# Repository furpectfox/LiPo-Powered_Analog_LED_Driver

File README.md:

# Lipo-Powered Analog LED Driver
This circuit controls the dimming of an LED bar using only ICs and analog components&mdash;no microcontroller required. [Watch the demo here](https://youtu.be/S3qqzCgYGNY)

## [Click Me for Schematic](KiCad/schematic.pdf)

### Toggle ON/OFF
The circuit uses a push button to toggle power ON and OFF. In the OFF state, it consumes approximately 150 µA, due to current leakage through pull-up resistors.  

### Automatic Power Down
The circuit automatically shuts down when the voltage drops to 3V. However, even in the OFF state, it still consumes 150 µA, so it does not protect the battery from discharging comepletely.  

### Driving the LED with an N-Channel MOSFET
***Voltage Doubler***: The mosfet I'm using is a N-Channel MOSFET [IRF3205](https://www.infineon.com/dgdl/Infineon-IRF3205-DataSheet-v01_01-EN.pdf?fileId=5546d462533600a4015355def244190a). It has a Gate Threshold Voltage (Vgs) ranging from 2.0V to 4.0V. The normal operating voltage of a LiPo 18650 battery is 3.7V, and it decreases as the battery is being depleted. The solution is to have a voltage multiplier circuit to boost the voltage seen by the mosfet's gate to nearly twice the battery's voltage. This ensures the voltage driving the mosfet is always higher than the gate-source threshold voltage, even as the battery voltage decreases over time.  

The yellow trace shows the battery voltage (~4V). The blue trace shows the boosted voltage (~8V).  

***PWM Generator for Mosfet***:  
* A LM339 voltage comparator generates a ~800Hz square wave.
* This signal passes through a low-pass filter, converting it into a (somewhat) triangular waveform.
* A second voltage comparator compares this triangular waveform with a variable DC reference voltage (generated by a Resistor Selector Circuit).
* The result is a PWM signal with a controllable duty cycle, which drives the MOSFET gate and controls LED brightness.

Below is an example of a 25% duty cycle PWM signal:
* Top image: Triangular wave (blue) vs. DC reference voltage (yellow). Adjusting the level of the DC reference votlage will vary the duty cycle of the output square wave.
* Bottom image: Resulting gate drive signal (blue) (~8V amplitude).  

The circuit also allows a gradual voltage fall at the MOSFET gate, preventing high reverse voltage spikes at the drain (caused by long wiring acting as an inductor).

## Prototype

## PCB Layout
***The PCB layout was designed for homemade single-sided PCB fabrication using [this PCB plotter attachment](https://github.com/furpectfox/PCB_Trace_Plotter)***  

## Finish

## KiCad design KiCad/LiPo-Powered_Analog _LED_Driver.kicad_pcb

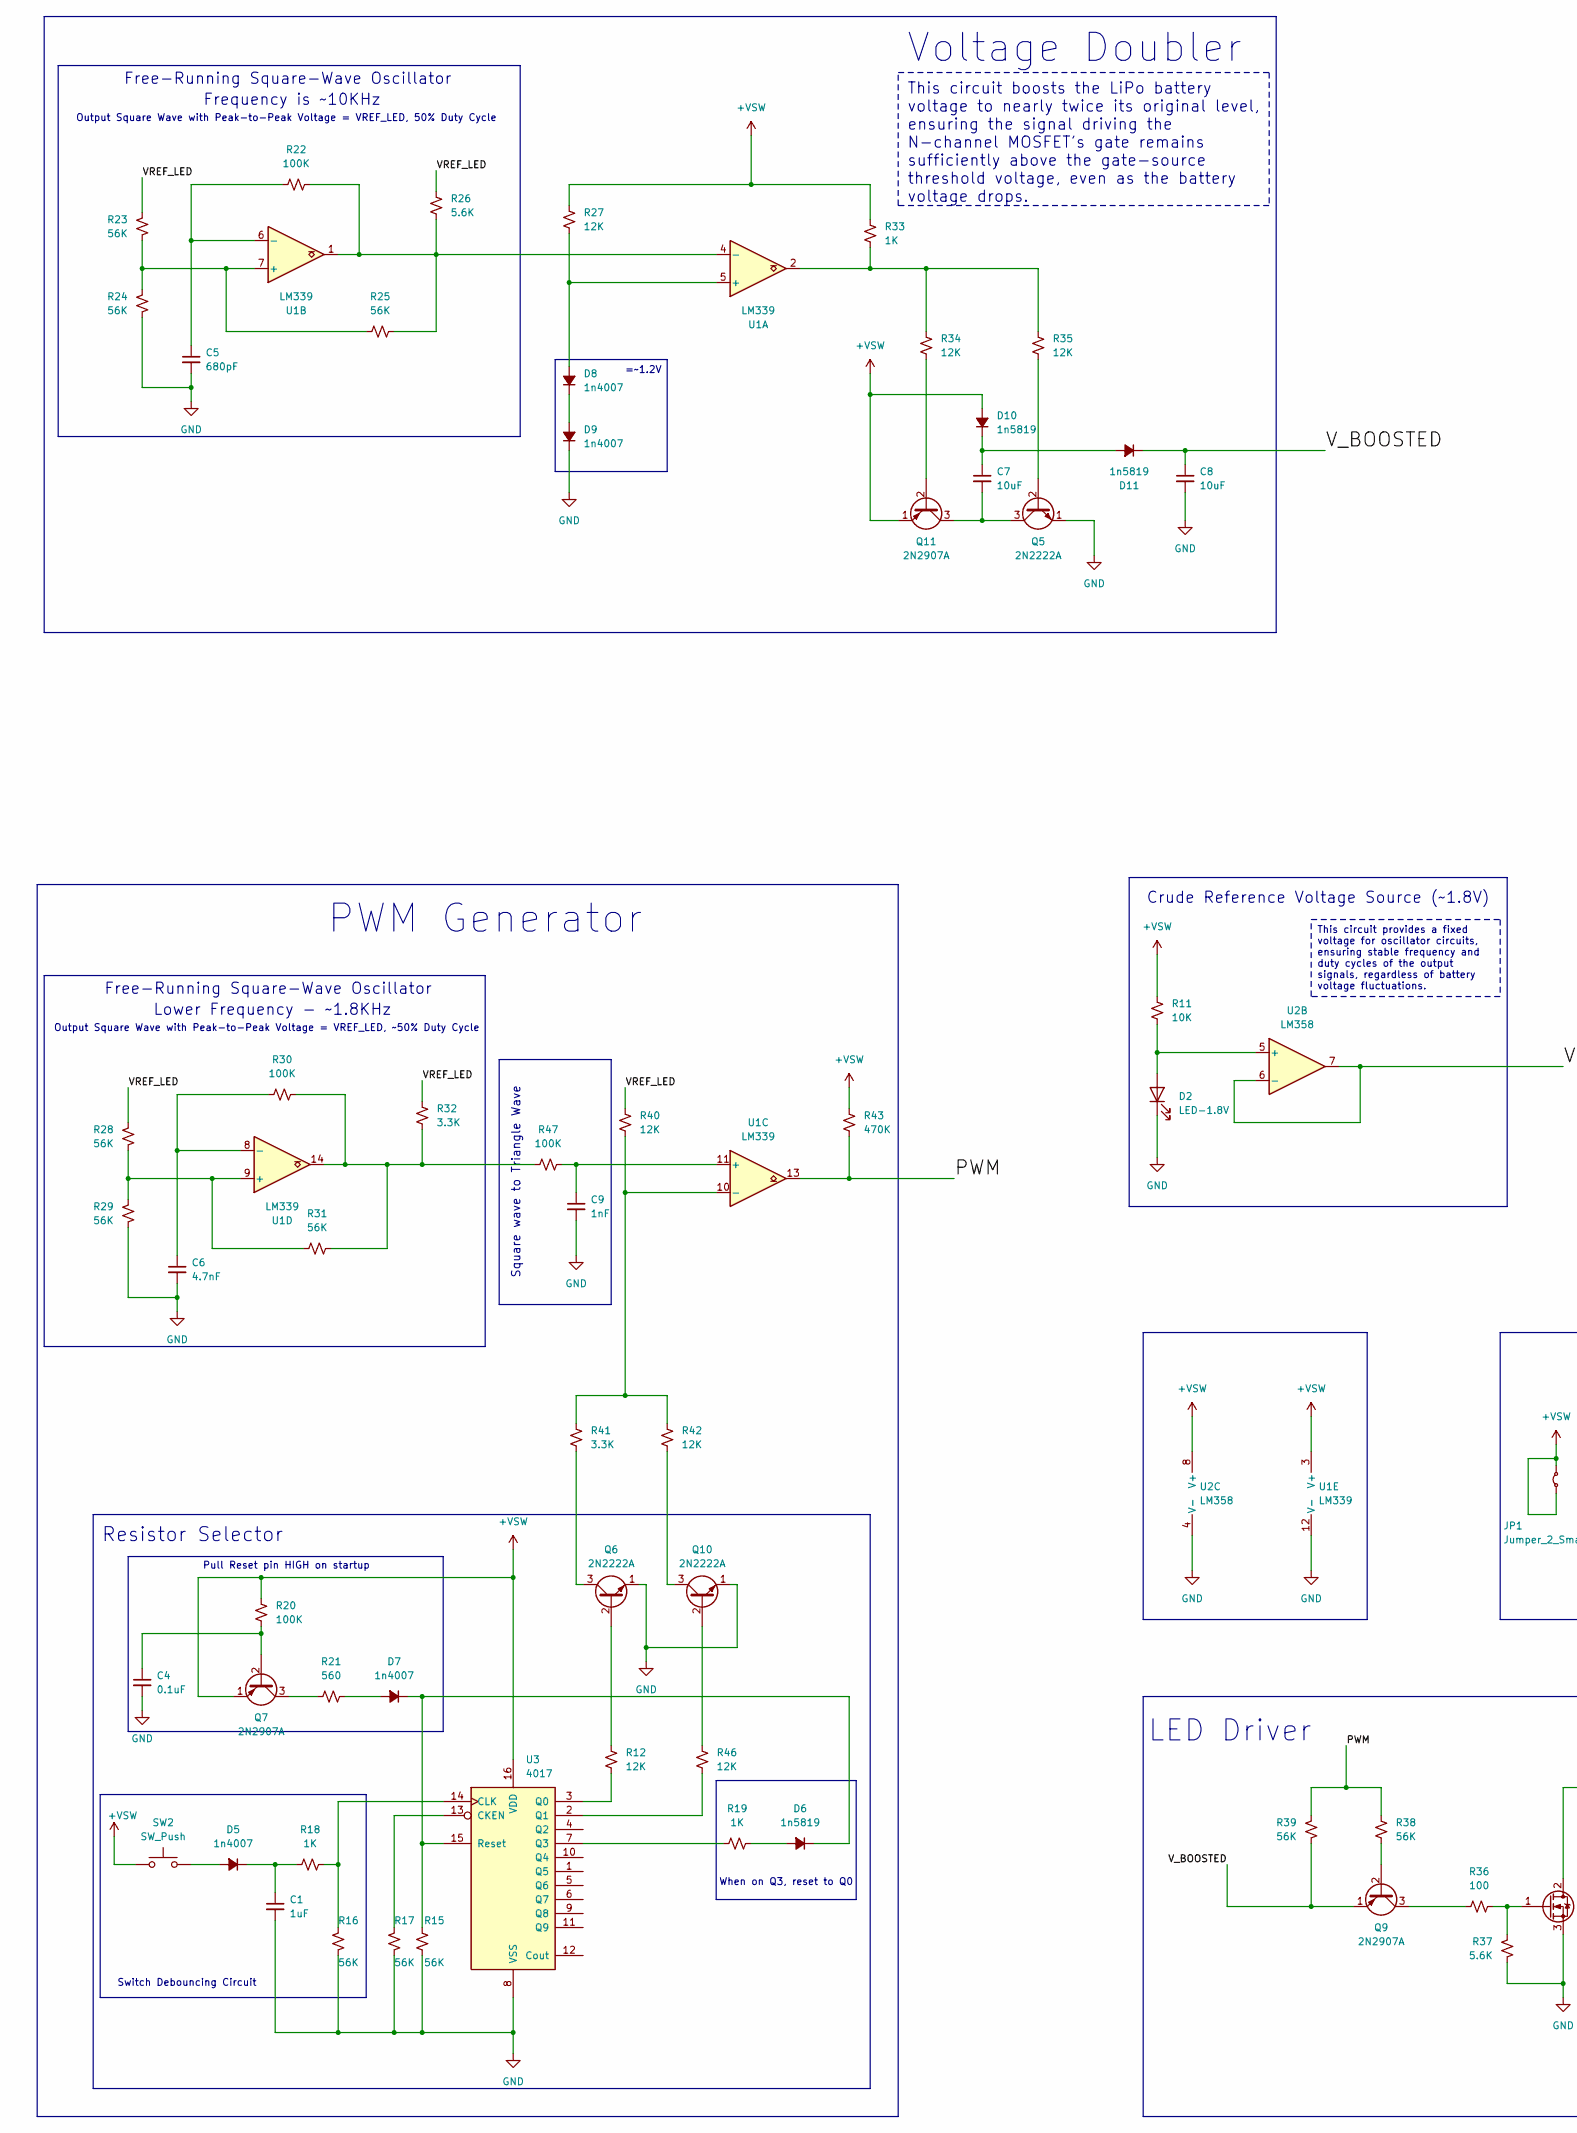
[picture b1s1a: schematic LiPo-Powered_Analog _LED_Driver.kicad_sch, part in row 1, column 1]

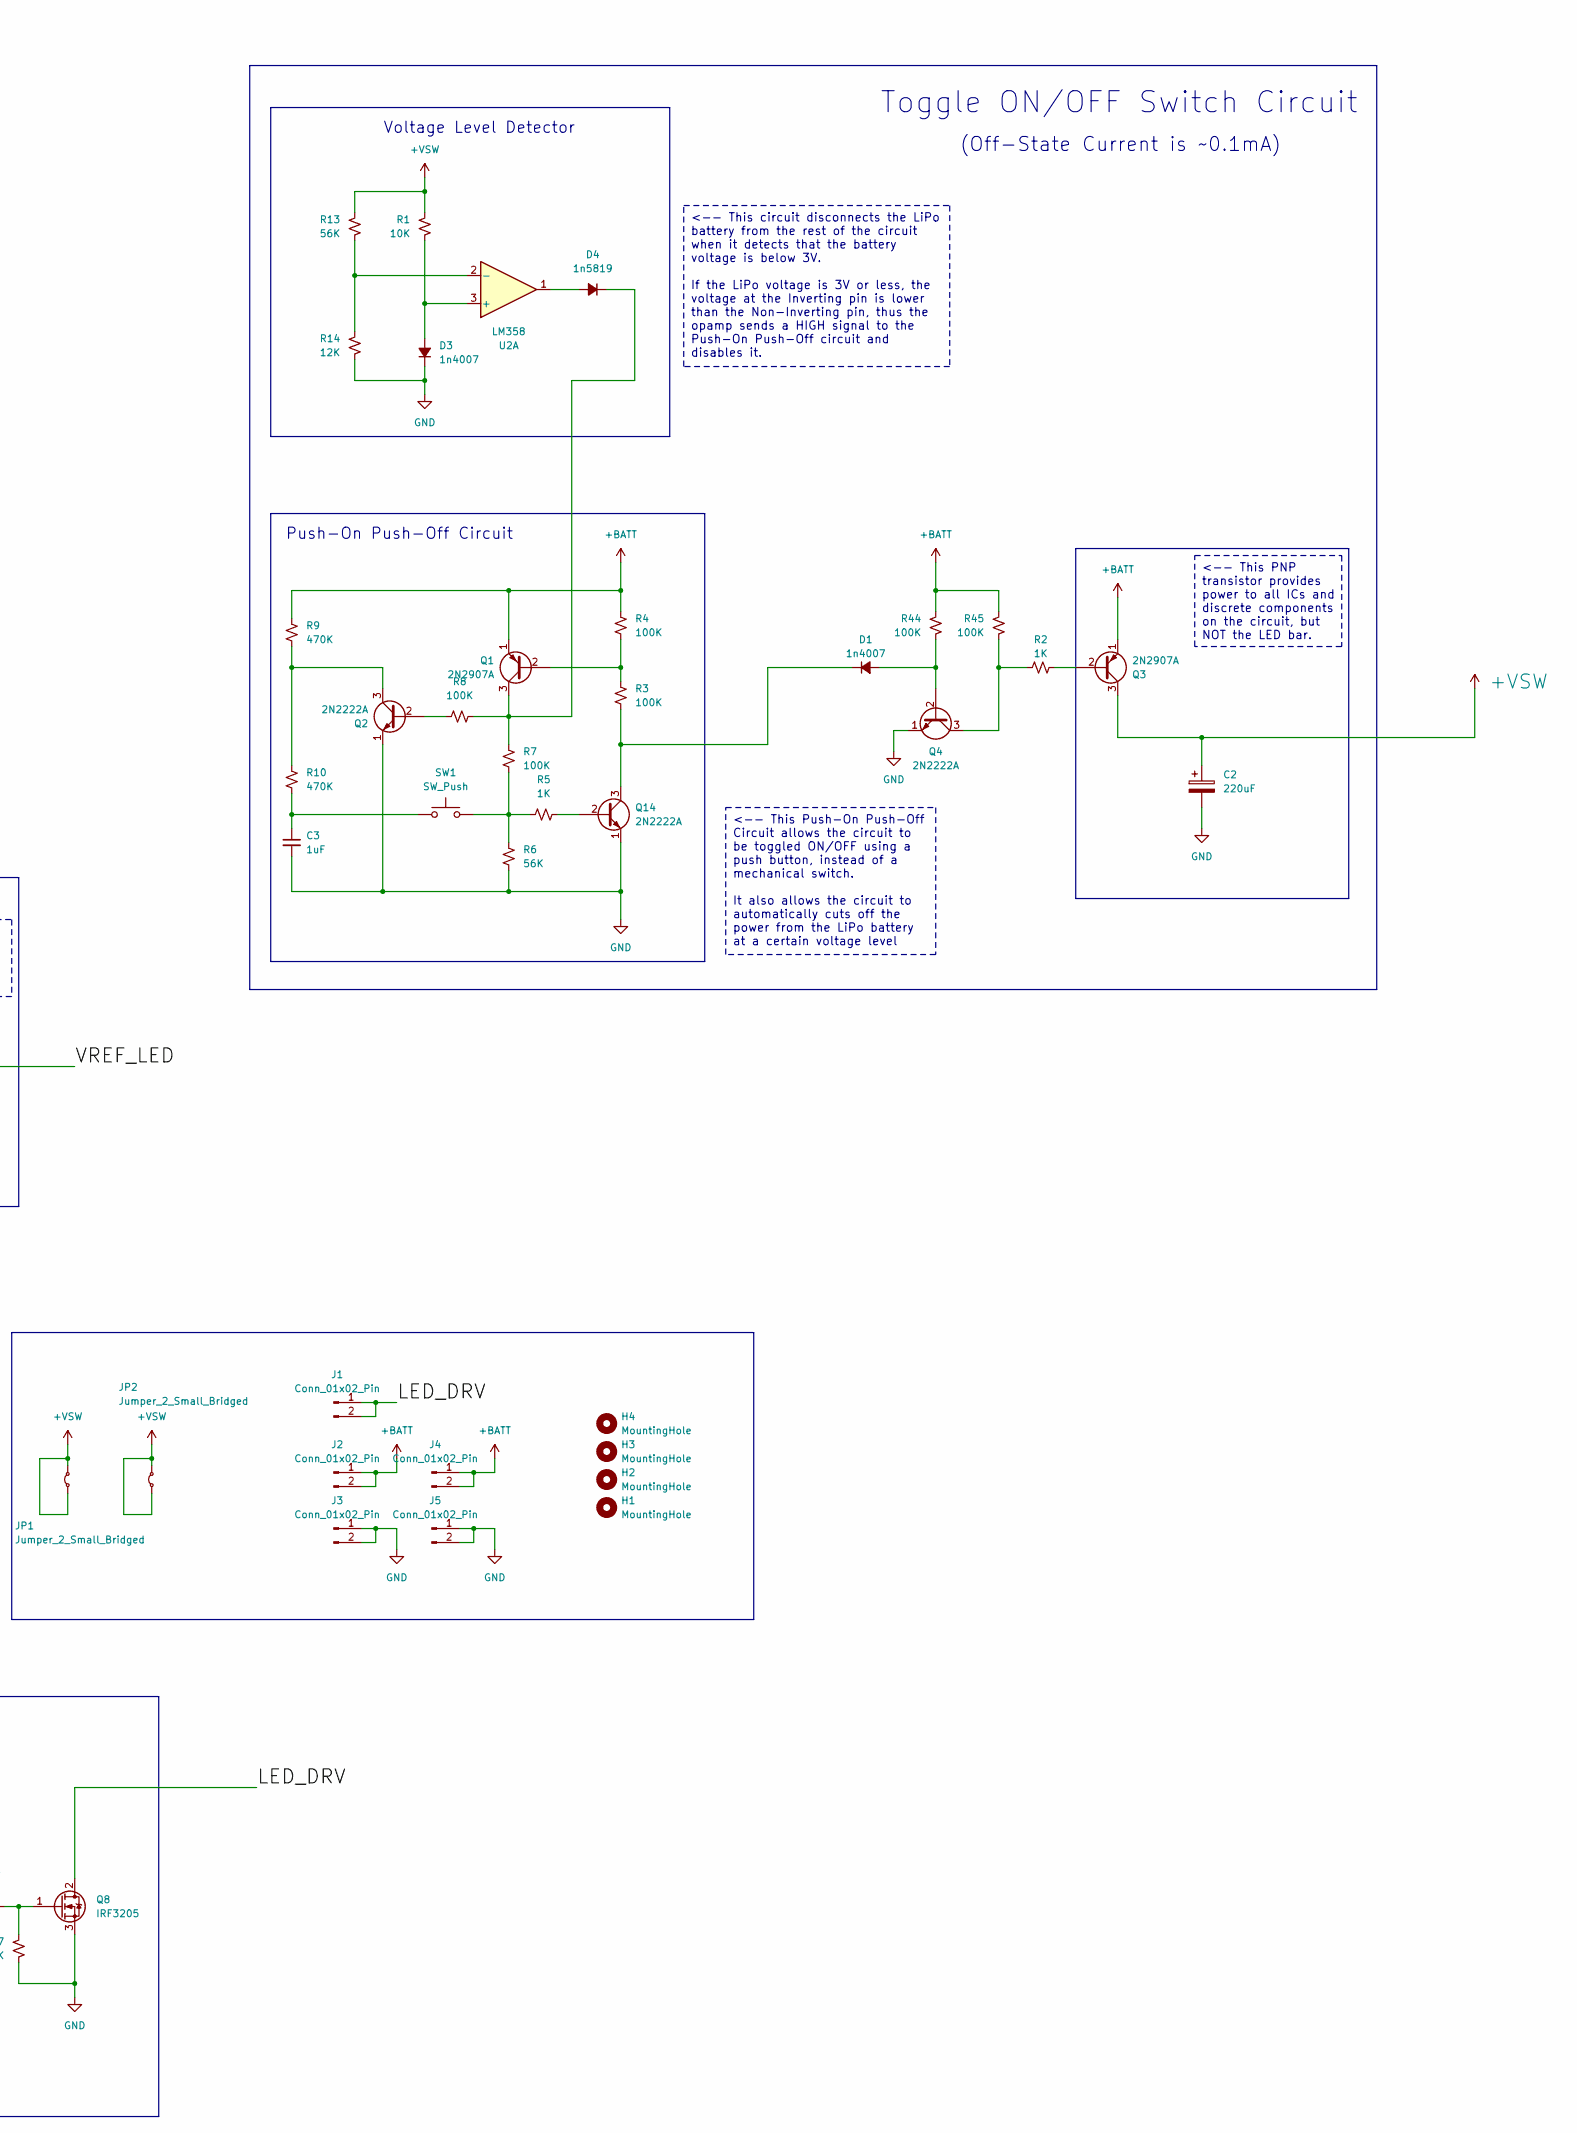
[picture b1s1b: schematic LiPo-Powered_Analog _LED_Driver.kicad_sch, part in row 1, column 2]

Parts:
C1, C3: 1uF; C_0603_1608Metric_Pad1.08x0.95mm_HandSolder
C2: 220uF; C_Radial_D6.3mm_H11.0mm_P2.50mm
C4: 0.1uF; C_0603_1608Metric_Pad1.08x0.95mm_HandSolder
C5: 680pF; C_0603_1608Metric_Pad1.08x0.95mm_HandSolder
C6: 4.7nF; C_0603_1608Metric_Pad1.08x0.95mm_HandSolder
C7, C8: 10uF; C_0603_1608Metric_Pad1.08x0.95mm_HandSolder
C9: 1nF; C_0603_1608Metric_Pad1.08x0.95mm_HandSolder
D1, D3, D5, D8, D9: 1n4007; D_SOD-123
D2: LED-1.8V; LED_0603_1608Metric_Pad1.05x0.95mm_HandSolder
D4, D6, D10, D11: 1n5819; D_A-405_P7.62mm_Horizontal
D7: 1n4007; D_A-405_P7.62mm_Horizontal
H1, H2, H3, H4: MountingHole; MountingHole_3.2mm_M3
J1, J2, J3, J4, J5: Conn_01x02_Pin; TestPoint_2Pads_Pitch5.08mm_Drill1.3mm
JP1, JP2: Jumper_2_Small_Bridged; TestPoint_2Pads_Pitch5.08mm_Drill1.3mm
Q1, Q3, Q7, Q9, Q11: 2N2907A; TO-92_Inline_Wide
Q2, Q4, Q5, Q6, Q10, Q14: 2N2222A; TO-92_Inline_Wide
Q8: IRF3205; TO-220-3_Horizontal_TabDown
R1: 10K; R_Axial_DIN0207_L6.3mm_D2.5mm_P7.62mm_Horizontal
R2, R5, R18, R19, R33: 1K; R_0603_1608Metric_Pad0.98x0.95mm_HandSolder
R3, R4, R7, R8, R20, R44, R45, R47: 100K; R_0603_1608Metric_Pad0.98x0.95mm_HandSolder
R6, R15, R16, R17, R23, R24, R29: 56K; R_0603_1608Metric_Pad0.98x0.95mm_HandSolder
R9, R10, R43: 470K; R_0603_1608Metric_Pad0.98x0.95mm_HandSolder
R11: 10K; R_0603_1608Metric_Pad0.98x0.95mm_HandSolder
R12, R40, R42, R46: 12K; R_Axial_DIN0207_L6.3mm_D2.5mm_P7.62mm_Horizontal
R13, R25, R28, R31, R38, R39: 56K; R_Axial_DIN0207_L6.3mm_D2.5mm_P7.62mm_Horizontal
R14, R27, R34, R35: 12K; R_0603_1608Metric_Pad0.98x0.95mm_HandSolder
R21: 560; R_0603_1608Metric_Pad0.98x0.95mm_HandSolder
R22, R30: 100K; R_Axial_DIN0207_L6.3mm_D2.5mm_P7.62mm_Horizontal
R26: 5.6K; R_Axial_DIN0207_L6.3mm_D2.5mm_P7.62mm_Horizontal
R32: 3.3K; R_0603_1608Metric_Pad0.98x0.95mm_HandSolder
R36: 100; R_0603_1608Metric_Pad0.98x0.95mm_HandSolder
R37: 5.6K; R_0603_1608Metric_Pad0.98x0.95mm_HandSolder
R41: 3.3K; R_Axial_DIN0207_L6.3mm_D2.5mm_P7.62mm_Horizontal
SW1, SW2: SW_Push; SolderWire-0.5sqmm_1x02_P4.6mm_D0.9mm_OD2.1mm
U1: LM339; DIP-14_W7.62mm
U2: LM358; DIP-8_W7.62mm
U3: 4017; DIP-16_W7.62mm

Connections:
+BATT: J2.1, J2.2, J4.1, J4.2, Q1.1 (E), Q3.1 (E), R4.1, R9.1, R44.1, R45.1
+VSW: C2.1, D10.2 (A), JP1.1 (A), JP1.2 (B), JP2.1 (A), JP2.2 (B), Q3.3 (C), Q7.1 (E), Q11.1 (E), R1.1, R11.1, R13.1, R20.1, R27.1, R33.1, R43.1, SW2.1, U1.3 (V+), U2.8 (V+), U3.16 (VDD)
/LED_DRV: J1.1, J1.2, Q8.2 (D)
/PWM: R38.2, R39.1, R43.2, U1.13
/VREF_LED: R23.1, R26.1, R28.1, R32.1, R40.1, U2.6 (-), U2.7
/V_BOOSTED: C8.1, D11.1 (K), Q9.1 (E), R39.2
GND: C1.2, C2.2, C3.2, C4.2, C5.2, C6.2, C8.2, C9.2, D2.1 (K), D3.1 (K), D9.1 (K), J3.1, J3.2, J5.1, J5.2, Q2.1 (E), Q4.1 (E), Q5.1 (E), Q6.1 (E), Q8.3 (S), Q10.1 (E), Q14.1 (E), R6.2, R14.2, R15.1, R16.1, R17.1, R24.2, R29.2, R37.1, U1.12 (V-), U2.4 (V-), U3.8 (VSS)
unnamed: C3.1, R10.2, SW1.1
unnamed: D1.2 (A), Q4.2 (B), R44.2
unnamed: D1.1 (K), Q14.3 (C), R3.2
unnamed: D2.2 (A), R11.2, U2.5 (+)
unnamed: D3.2 (A), R1.2, U2.3 (+)
unnamed: D4.2 (A), U2.1
unnamed: D4.1 (K), Q1.3 (C), R7.1, R8.2
unnamed: D5.2 (A), SW2.2
unnamed: C1.1, D5.1 (K), R18.1
unnamed: D6.2 (A), R19.2
unnamed: D6.1 (K), D7.1 (K), R15.2, U3.15 (Reset)
unnamed: D7.2 (A), R21.2
unnamed: D8.2 (A), R27.2, U1.5 (+)
unnamed: D8.1 (K), D9.2 (A)
unnamed: C7.1, D10.1 (K), D11.2 (A)
unnamed: Q1.2 (B), R3.1, R4.2
unnamed: Q2.2 (B), R8.1
unnamed: Q2.3 (C), R9.2, R10.1
unnamed: Q3.2 (B), R2.2
unnamed: Q4.3 (C), R2.1, R45.2
unnamed: Q5.2 (B), R35.1
unnamed: Q6.2 (B), R12.1
unnamed: Q6.3 (C), R41.2
unnamed: C4.1, Q7.2 (B), R20.2
unnamed: Q7.3 (C), R21.1
unnamed: Q8.1 (G), R36.2, R37.2
unnamed: Q9.2 (B), R38.1
unnamed: Q9.3 (C), R36.1
unnamed: Q10.2 (B), R46.1
unnamed: Q10.3 (C), R42.2
unnamed: Q11.2 (B), R34.1
unnamed: C7.2, Q5.3 (C), Q11.3 (C)
unnamed: Q14.2 (B), R5.2
unnamed: R5.1, R6.1, R7.2, SW1.2
unnamed: R30.2, R31.2, R32.2, R47.1, U1.14
unnamed: R33.2, R34.2, R35.2, U1.2
unnamed: R22.2, R25.2, R26.2, U1.1, U1.4 (-)
unnamed: R23.2, R24.1, R25.1, U1.7 (+)
unnamed: C5.1, R22.1, U1.6 (-)
unnamed: C9.1, R47.2, U1.11 (+)
unnamed: R40.2, R41.1, R42.1, U1.10 (-)
unnamed: R28.2, R29.1, R31.1, U1.9 (+)
unnamed: C6.1, R30.1, U1.8 (-)
unnamed: R13.2, R14.1, U2.2 (-)
unnamed: R17.2, U3.13 (CKEN)
unnamed: R16.2, R18.2, U3.14 (CLK)
unnamed: R12.2, U3.3 (Q0)
unnamed: R46.2, U3.2 (Q1)
unnamed: R19.1, U3.7 (Q3)

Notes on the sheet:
<-- This circuit disconnects the LiPo battery from the rest of the circuit when it detects that the battery voltage is below 3V. If the LiPo voltage is 3V or less, the voltage at the Inverting pin is lower than the Non-Inverting pin, thus the opamp sends a HIGH signal to the Push-On Push-Off circui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
This circuit boosts the LiPo battery voltage to nearly twice its original level, ensuring the signal driving the N-channel MOSFET's gate remains sufficiently above the gate-source threshold voltage, even as the battery voltage drops.
<-- This Push-On Push-Off Circuit allows the circuit to be toggled ON/OFF using a push button, instead of a mechanical switch. It also allows the circuit to automatically cuts off the power from the LiPo battery at a certain voltage level
<-- This PNP transistor provides power to all ICs and discrete components on the circuit, but NOT the LED bar.
This circuit provides a fixed voltage for oscillator circuits, ensuring stable frequency and duty cycles of the output signals, regardless of battery voltage fluctuations.
LED Driver
Frequency is ~10KHz
Crude Reference Voltage Source (~1.8V)
Voltage Level Detector
Free-Running Square-Wave Oscillator
Push-On Push-Off Circuit
PWM Generator
Output Square Wave with Peak-to-Peak Voltage = VREF_LED, 50% Duty Cycle
Resistor Selector
Lower Frequency - ~1.8KHz
Toggle ON/OFF Switch Circuit
Square wave to Triangle Wave
When on Q3, reset to Q0
Output Square Wave with Peak-to-Peak Voltage = VREF_LED, ~50% Duty Cycle
(Off-State Current is ~0.1mA)
Voltage Doubler
=~1.2V
Pull Reset pin HIGH on startup
Switch Debouncing Circuit

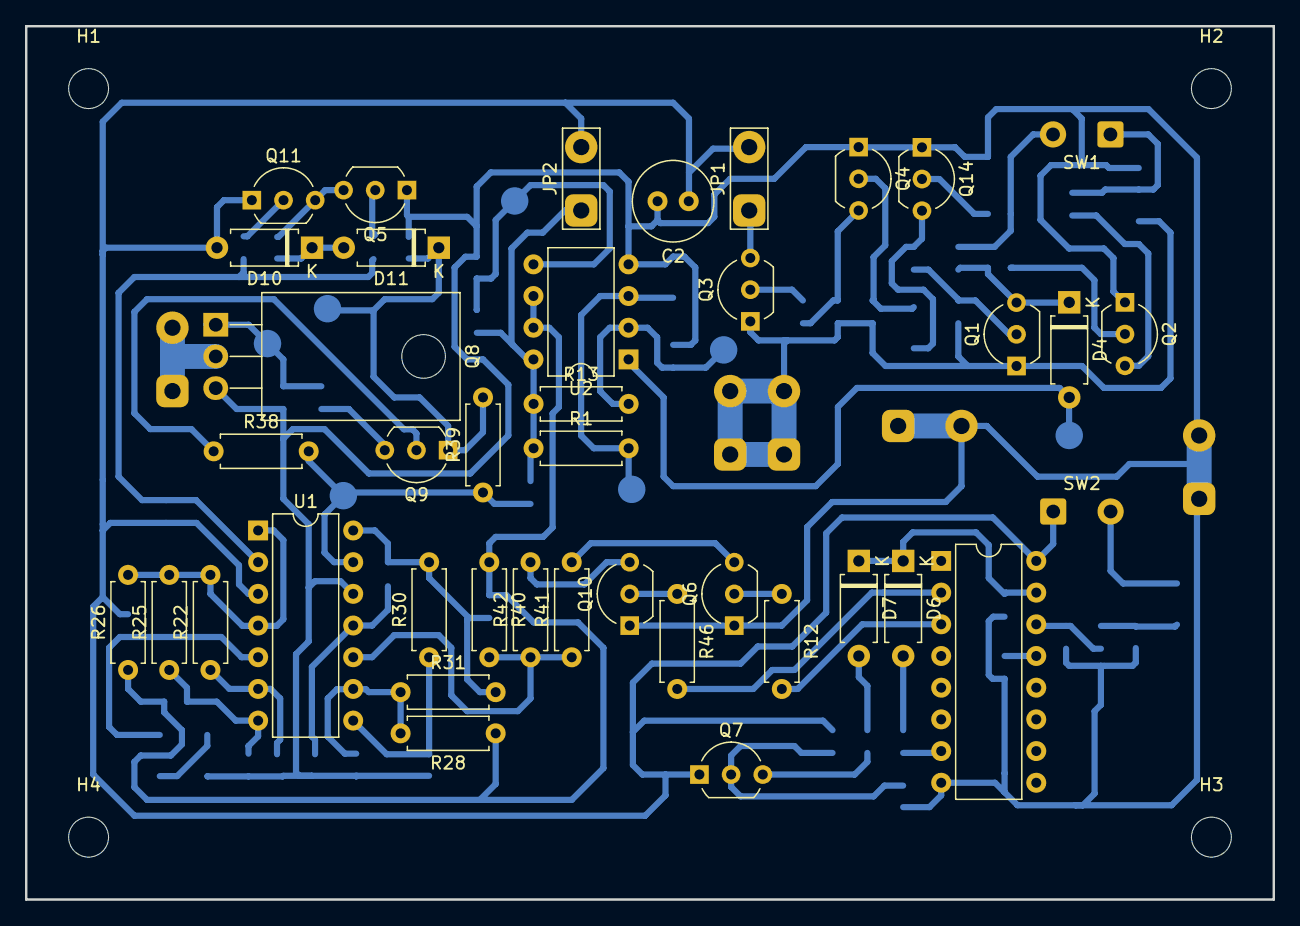
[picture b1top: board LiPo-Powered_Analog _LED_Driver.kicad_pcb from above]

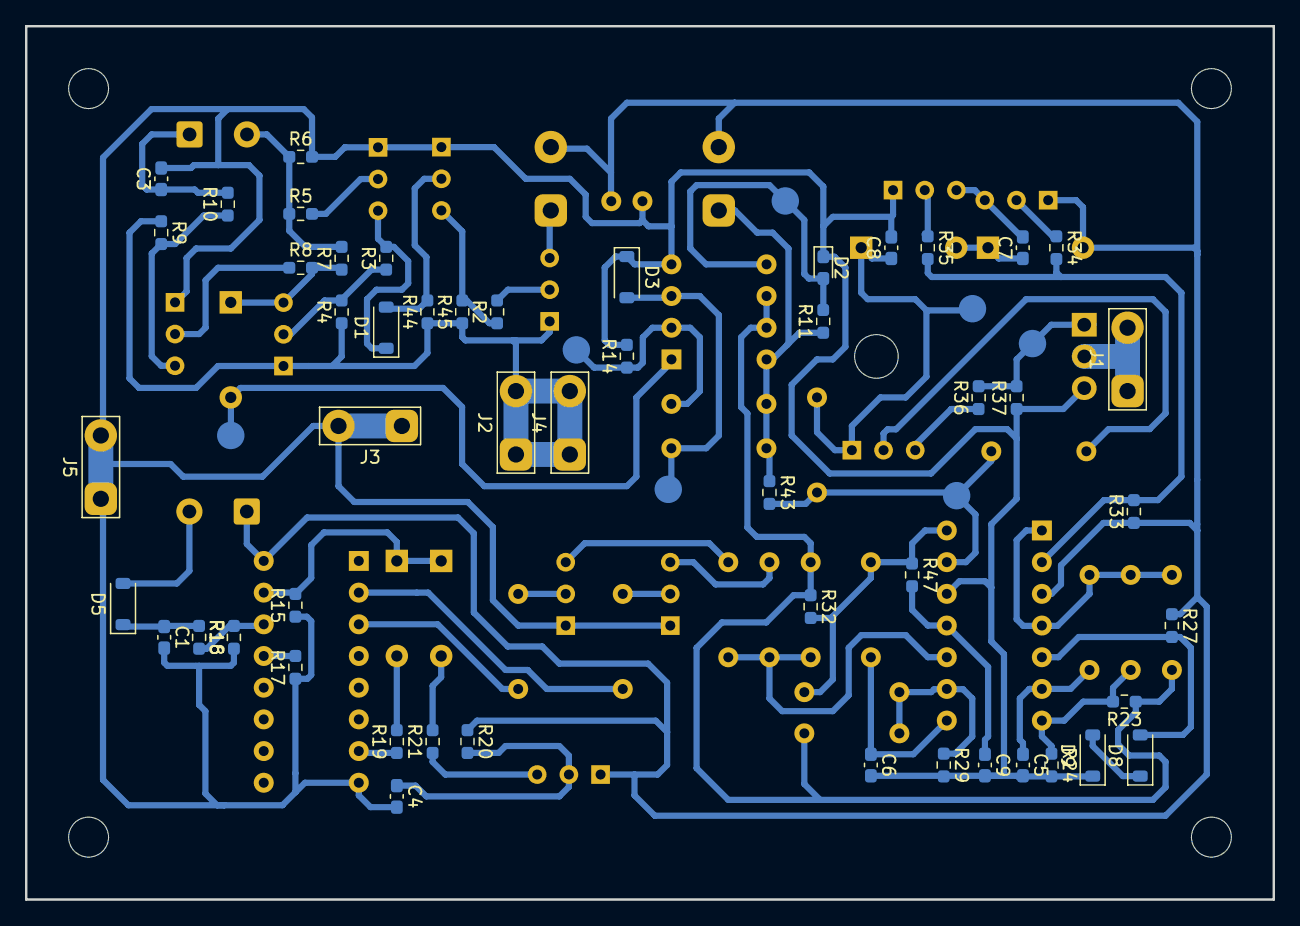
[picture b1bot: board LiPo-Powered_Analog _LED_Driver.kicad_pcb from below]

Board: 2 copper layers, 100.0 x 70.0 mm, 95 parts (51 on the bottom side), 56 nets.

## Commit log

2025-03-03 add schematic
2025-03-09 update schematic. Add PCB layout
2025-03-09 Add file to KiCad folder
2025-03-12 Update schematic and PCB layout. Add images
2025-03-12 add images
